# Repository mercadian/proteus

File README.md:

# Proteus

This repository contains the resources for creating and working with the Proteus.

*For documentation on setting up and using the Proteus, please see the **Wiki** tab above.*

*For the source code used to build the OS image that the Proteus comes with: please see the [proteus-image](https://github.com/mercadian/proteus-image) repository.*

## Contents

**labels** - contains `lumi` files for the model / serial number label on the bottom of the Proteus and the danger label attached to the power supply cable. Use the [Desktop Supplies editor](https://designer.desktopsupplies.com/?page_id=16&product_base=57&product_cms=127) to work with them, item template 62015.

**models** - contains the STL files used to print the Proteus case components.

**pcbs** - contains complete [KiCAD](https://www.kicad.org/) projects for supplemental PCBs used by the Proteus (for example, the front panel). Use KiCAD v6.0.11+.

**vanity-plate** - contains instructions and a sample for creating an image used to etch the Proteus's front aluminum vanity plate and other samples that have been made available for public consumption by generous customers.

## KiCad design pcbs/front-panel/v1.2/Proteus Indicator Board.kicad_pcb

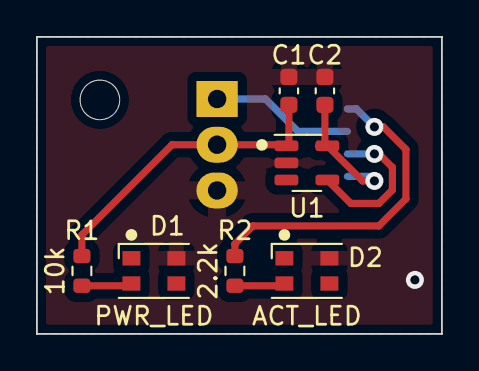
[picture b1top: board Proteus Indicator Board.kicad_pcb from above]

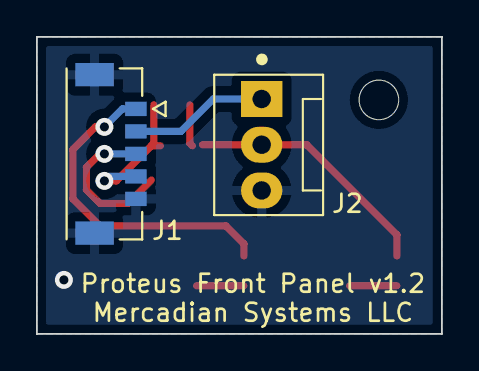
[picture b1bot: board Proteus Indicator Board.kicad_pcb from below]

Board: 2 copper layers, 22.5 x 16.5 mm, 9 parts (2 on the bottom side), 8 nets.

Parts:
C1, C2: 0.1uF; C_0603_1608Metric
D1: PWR_LED; LED_Cree-PLCC4_3.2x2.8mm_CCW
D2: ACT_LED; LED_Cree-PLCC4_3.2x2.8mm_CCW
J1: 5055670571; MOLEX_5055670571
J2: 640454-3; FanPinHeader_1x03_P2.54mm_Vertical
R1: 10k; R_0603_1608Metric
R2: 2.2k; R_0603_1608Metric
U1: AP2171W; SOT-23-5

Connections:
/3.3v: J1.3 (3.3v), U1.4 (EN)
/5v: C1.1, J2.2 (+5V), R1.1, U1.1 (OUT)
/5v_IN: C2.1, J1.4 (5v), U1.5 (IN)
/ACT_LED: J1.1 (Activity), R2.1
/Fan_Tach: J1.2 (Fan_Tach), J2.1 (Tach)
Earth: C1.2, C2.2, D1.1 (K), D2.1 (K), J1.5 (GND), J1.S1, J1.S2, J2.3 (GND), U1.2 (GND)
unnamed: D1.2 (A), R1.2
unnamed: D2.2 (A), R2.2

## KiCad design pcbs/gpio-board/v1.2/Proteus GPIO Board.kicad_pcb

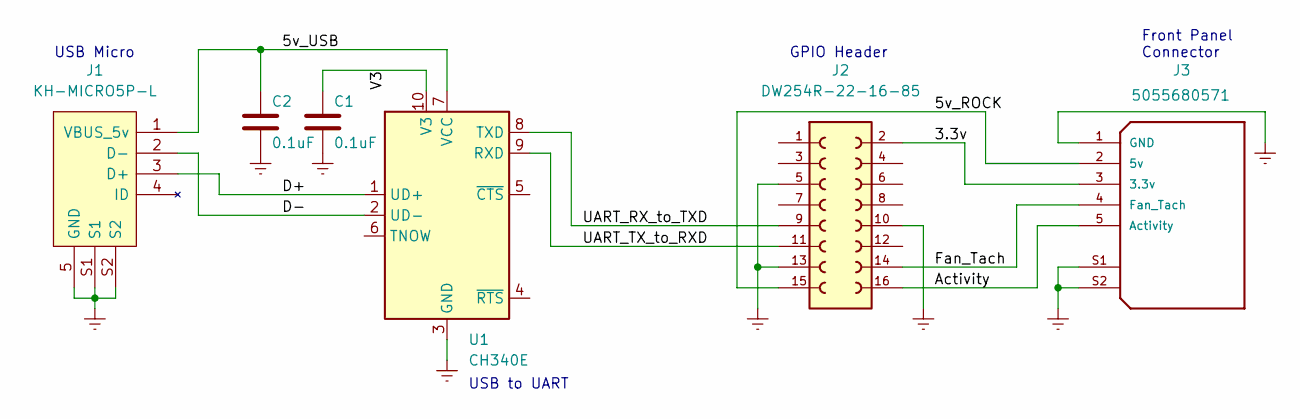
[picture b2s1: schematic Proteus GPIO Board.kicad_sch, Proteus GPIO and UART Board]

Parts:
C1, C2: 0.1uF; C_0603_1608Metric
J1: KH-MICRO5P-L; GCT_USB3131-30-0230-A_REVB; JLC C962220
J2: DW254R-22-16-85; 61301621821; JLC C2935989
J3: 5055680571; MOLEX_5055680571; PARTREV C; JLC C585386
U1: CH340E; MSOP-10_3x3mm_P0.5mm; JLC C99652

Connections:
/3.3v: J2.2, J3.3 (3.3v)
/5v_ROCK: J2.15, J3.2 (5v)
/5v_USB: C2.1, J1.1 (VBUS_5v), U1.7 (VCC)
/Activity: J2.16, J3.5 (Activity)
/D+: J1.3 (D+), U1.1 (UD+)
/D-: J1.2 (D-), U1.2 (UD-)
/Fan_Tach: J2.14, J3.4 (Fan_Tach)
/UART_RX_to_TXD: J2.9, U1.8 (TXD)
/UART_TX_to_RXD: J2.11, U1.9 (RXD)
/V3: C1.1, U1.10 (V3)
Earth: C1.2, C2.2, J1.5 (GND), J1.S1, J1.S2, J2.5, J2.10, J2.13, J3.1 (GND), J3.S1, J3.S2, U1.3 (GND)

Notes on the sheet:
GPIO Header
USB to UART
USB Micro
Front Panel Connector

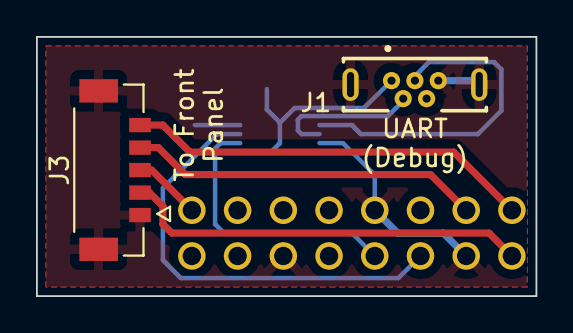
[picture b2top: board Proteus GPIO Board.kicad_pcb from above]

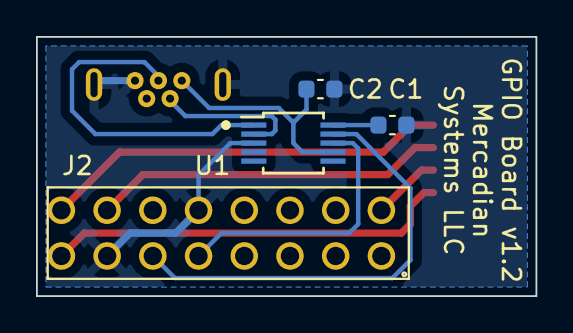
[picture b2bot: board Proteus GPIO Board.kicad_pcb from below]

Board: 2 copper layers, 27.8 x 14.4 mm, 6 parts (4 on the bottom side), 11 nets.

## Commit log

2023-01-21 Initial artifact commit
2023-05-07 Added v1.1 and v1.2 artifacts
2023-05-14 Updated models for the new printer
2023-05-14 Added Fusion project for the v1.1 case
